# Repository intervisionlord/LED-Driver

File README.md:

# LED-Driver

Схема для управления RGB LED Лентой при помощи пульта от телевизора

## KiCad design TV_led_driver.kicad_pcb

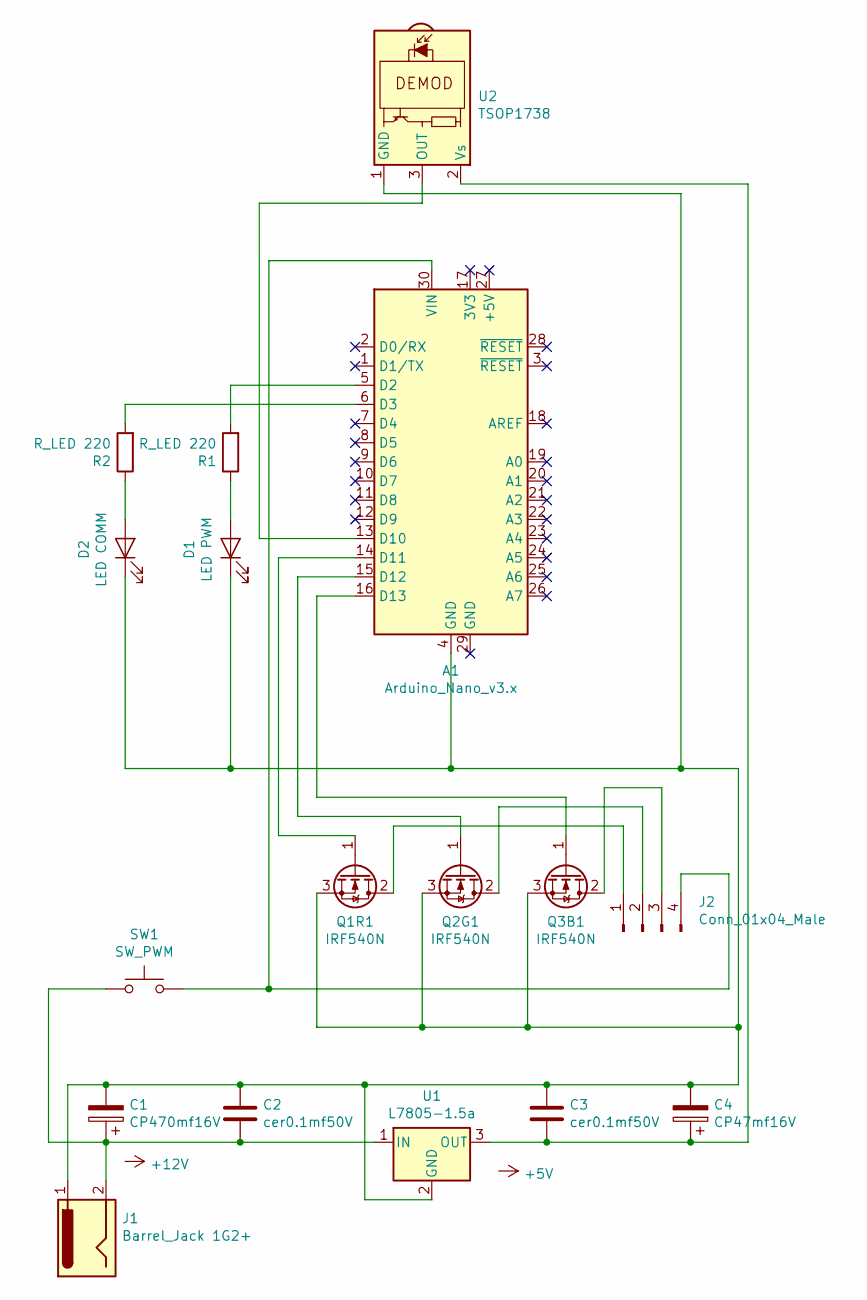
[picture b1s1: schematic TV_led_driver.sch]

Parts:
A1: Arduino_Nano_v3.x; Arduino_Nano
C1: CP470mf16V; CP_Radial_D8.0mm_P3.50mm
C2, C3: cer0.1mf50V; C_Disc_D7.0mm_W2.5mm_P5.00mm
C4: CP47mf16V; CP_Radial_D5.0mm_P2.50mm
D1: LED PWM; LED_D3.0mm_Horizontal_O1.27mm_Z6.0mm
D2: LED COMM; LED_D3.0mm_Horizontal_O1.27mm_Z6.0mm
J1: Barrel_Jack 1G2+; BarrelJack_CUI_PJ-063AH_Horizontal
J2: Conn_01x04_Male; JST_EH_S4B-EH_1x04_P2.50mm_Horizontal
Q1R1, Q2G1, Q3B1: IRF540N; TO-220-3_Vertical
R1, R2: R_LED 220; R_Axial_DIN0207_L6.3mm_D2.5mm_P7.62mm_Horizontal
SW1: SW_PWM; SW_E-Switch_EG1224_SPDT_Angled
U1: L7805-1.5a; TO-220-3_Vertical
U2: TSOP1738; Vishay_CAST-3Pin

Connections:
unnamed: A1.4 (GND), C1.2, C2.1, C3.1, C4.2, D1.1 (K), D2.1 (K), J1.1, Q1R1.3 (S), Q2G1.3 (S), Q3B1.3 (S), U1.2 (GND), U2.1 (GND)
unnamed: A1.5 (D2), R1.2
unnamed: A1.6 (D3), R2.2
unnamed: A1.13 (D10), U2.3 (OUT)
unnamed: A1.14 (D11), Q1R1.1 (G)
unnamed: A1.15 (D12), Q2G1.1 (G)
unnamed: A1.16 (D13), Q3B1.1 (G)
unnamed: A1.30 (VIN), J2.4, SW1.2
unnamed: C1.1, C2.2, J1.2, SW1.1, U1.1 (IN)
unnamed: C3.2, C4.1, U1.3 (OUT), U2.2 (Vs)
unnamed: D1.2 (A), R1.1
unnamed: D2.2 (A), R2.1
unnamed: J2.1, Q1R1.2 (D)
unnamed: J2.2, Q2G1.2 (D)
unnamed: J2.3, Q3B1.2 (D)

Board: 2 copper layers, 25 parts (0 on the bottom side), 15 nets, no tracks yet.

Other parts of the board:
HEATSINK: Heatsink_132_32x14mm_2xFixation1.5mm; Heatsink_Stonecold_HS-132_32x14mm_2xFixation1.5mm
LOGO02: OSHW-Logo; OSHW-Logo2_7.3x6mm_SilkScreen
LOGO03: WEEE-Logo; WEEE-Logo_4.2x6mm_SilkScreen
Logo_DWK: KiCad-Logo2_5mm_SilkScreen
MNT1, MNT2, MNT3: MNT_2.5mm_Pad; MountingHole_2.5mm_Pad
MNT4: MNTHole_2.5mm_Pad; MountingHole_2.5mm_Pad

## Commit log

2020-02-13 Initial commit
    v.0.2

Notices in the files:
TV_led_driver.kicad_pcb:
© 2020 Intervision
